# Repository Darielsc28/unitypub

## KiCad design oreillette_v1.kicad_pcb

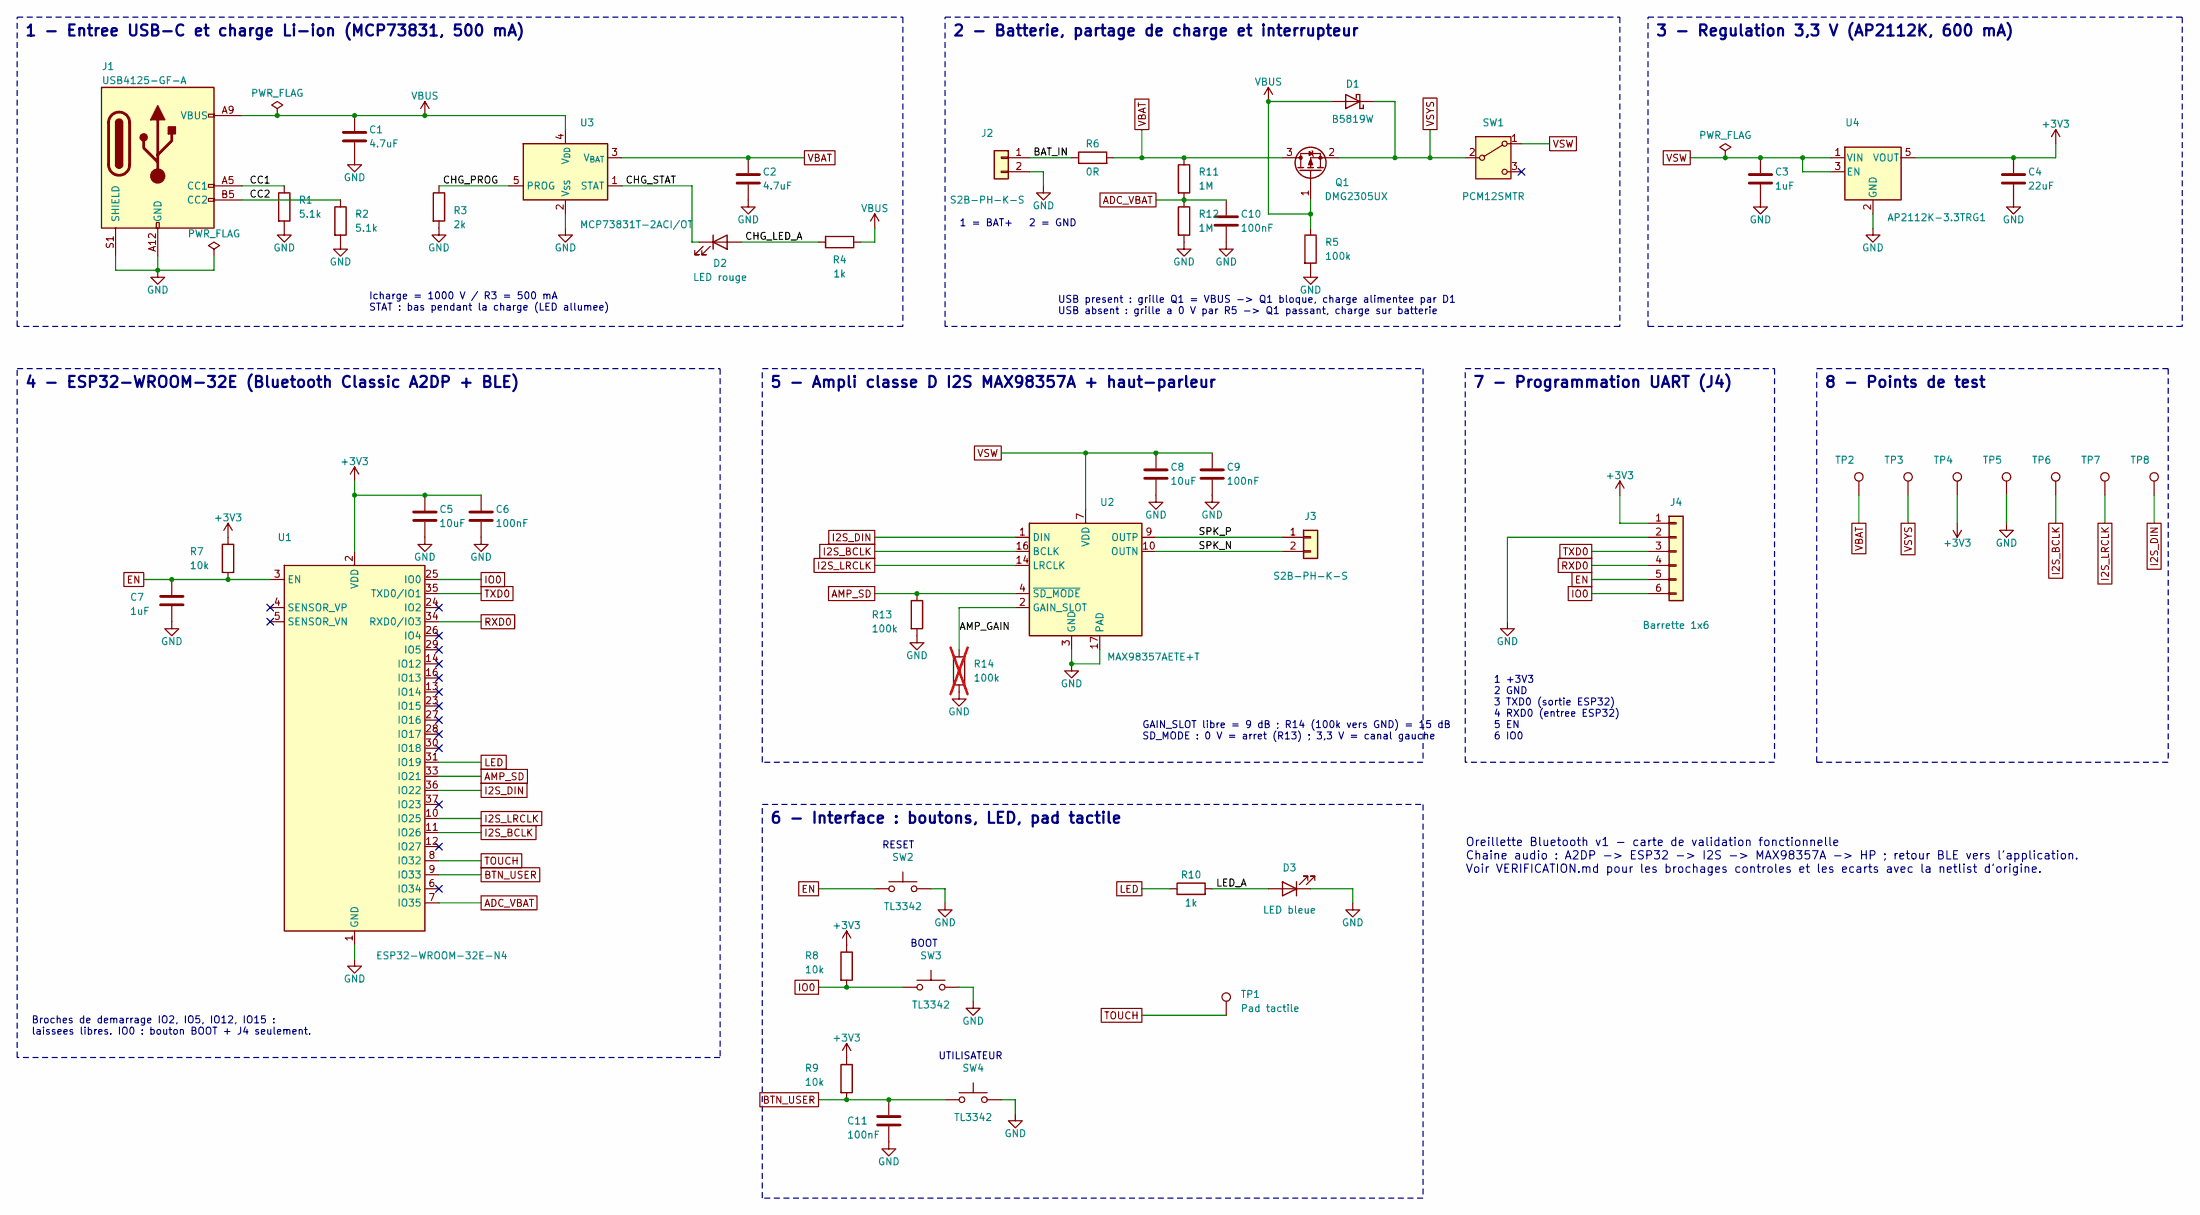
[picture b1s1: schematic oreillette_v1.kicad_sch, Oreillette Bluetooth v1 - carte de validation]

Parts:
C1, C2: 4.7uF; C_0603_1608Metric
C3, C7: 1uF; C_0603_1608Metric
C4: 22uF; C_0805_2012Metric
C5, C8: 10uF; C_0805_2012Metric
C6, C9, C10, C11: 100nF; C_0603_1608Metric
D1: B5819W; D_SOD-123
D2: LED rouge; LED_0603_1608Metric
D3: LED bleue; LED_0603_1608Metric
J1: USB4125-GF-A; USB_C_Receptacle_GCT_USB4125-xx-x_6P_TopMnt_Horizontal
J2, J3: S2B-PH-K-S; JST_PH_S2B-PH-K_1x02_P2.00mm_Horizontal
J4: Barrette 1x6; PinHeader_1x06_P2.54mm_Vertical
Q1: DMG2305UX; SOT-23
R1, R2: 5.1k; R_0603_1608Metric
R3: 2k; R_0603_1608Metric
R4, R10: 1k; R_0603_1608Metric
R5, R13: 100k; R_0603_1608Metric
R6: 0R; R_0603_1608Metric
R7, R8, R9: 10k; R_0603_1608Metric
R11, R12: 1M; R_0603_1608Metric
R14: 100k; R_0603_1608Metric; not fitted
SW1: PCM12SMTR; SW_SPDT_PCM12
SW2, SW3, SW4: TL3342; SW_SPST_TL3342
TP1: Pad tactile; TestPoint_Pad_D4.0mm
TP2: TP VBAT; TestPoint_Pad_D1.5mm
TP3: TP VSYS; TestPoint_Pad_D1.5mm
TP4: TP +3V3; TestPoint_Pad_D1.5mm
TP5: TP GND; TestPoint_Pad_D1.5mm
TP6: TP I2S_BCLK; TestPoint_Pad_D1.5mm
TP7: TP I2S_LRCLK; TestPoint_Pad_D1.5mm
TP8: TP I2S_DIN; TestPoint_Pad_D1.5mm
U1: ESP32-WROOM-32E-N4; ESP32-WROOM-32E
U2: MAX98357AETE+T; TQFN-16-1EP_3x3mm_P0.5mm_EP1.23x1.23mm
U3: MCP73831T-2ACI/OT; SOT-23-5
U4: AP2112K-3.3TRG1; SOT-23-5

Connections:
+3V3: C4.1, C5.1, C6.1, J4.1, R7.1, R8.1, R9.1, TP4.1, U1.2 (VDD), U4.5 (VOUT)
/AMP_GAIN: R14.1, U2.2 (GAIN_SLOT)
/BAT_IN: J2.1, R6.1
/CC1: J1.A5 (CC1), R1.1
/CC2: J1.B5 (CC2), R2.1
/CHG_LED_A: D2.2 (A), R4.2
/CHG_PROG: R3.1, U3.5 (PROG)
/CHG_STAT: D2.1 (K), U3.1 (STAT)
/LED_A: D3.2 (A), R10.2
/SPK_N: J3.2, U2.10 (OUTN)
/SPK_P: J3.1, U2.9 (OUTP)
ADC_VBAT: C10.1, R11.2, R12.1, U1.7 (IO35)
AMP_SD: R13.1, U1.33 (IO21), U2.4 (~SD_MODE)
BTN_USER: C11.1, R9.2, SW4.1, U1.9 (IO33)
EN: C7.1, J4.5, R7.2, SW2.1, U1.3 (EN)
GND: C1.2, C2.2, C3.2, C4.2, C5.2, C6.2, C7.2, C8.2, C9.2, C10.2, C11.2, D3.1 (K), J1.A12 (GND), J1.B12 (GND), J1.S1 (SHIELD), J2.2, J4.2, R1.2, R2.2, R3.2, R5.2, R12.2, R13.2, R14.2, SW2.2, SW3.2, SW4.2, TP5.1, U1.1 (GND), U1.15 (GND), U1.38 (GND), U1.39 (GND), U2.3 (GND), U2.11 (GND), U2.15 (GND), U2.17 (PAD), U3.2 (V_{SS}), U4.2 (GND)
I2S_BCLK: TP6.1, U1.11 (IO26), U2.16 (BCLK)
I2S_DIN: TP8.1, U1.36 (IO22), U2.1 (DIN)
I2S_LRCLK: TP7.1, U1.10 (IO25), U2.14 (LRCLK)
IO0: J4.6, R8.2, SW3.1, U1.25 (IO0)
LED: R10.1, U1.31 (IO19)
RXD0: J4.4, U1.34 (RXD0/IO3)
TOUCH: TP1.1, U1.8 (IO32)
TXD0: J4.3, U1.35 (TXD0/IO1)
VBAT: C2.1, Q1.3 (D), R6.2, R11.1, TP2.1, U3.3 (V_{BAT})
VBUS: C1.1, D1.2 (A), J1.A9 (VBUS), J1.B9 (VBUS), Q1.1 (G), R4.1, R5.1, U3.4 (V_{DD})
VSW: C3.1, C8.1, C9.1, SW1.1 (A), U2.7 (VDD), U2.8 (VDD), U4.1 (VIN), U4.3 (EN)
VSYS: D1.1 (K), Q1.2 (S), SW1.2 (B), TP3.1

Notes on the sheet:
1 - Entree USB-C et charge Li-ion (MCP73831, 500 mA)
Icharge = 1000 V / R3 = 500 mA STAT : bas pendant la charge (LED allumee)
2 - Batterie, partage de charge et interrupteur
1 = BAT+ 2 = GND
USB present : grille Q1 = VBUS -> Q1 bloque, charge alimentee par D1 USB absent : grille a 0 V par R5 -> Q1 passant, charge sur batterie
3 - Regulation 3,3 V (AP2112K, 600 mA)
4 - ESP32-WROOM-32E (Bluetooth Classic A2DP + BLE)
Broches de demarrage IO2, IO5, IO12, IO15 : laissees libres. IO0 : bouton BOOT + J4 seulement.
5 - Ampli classe D I2S MAX98357A + haut-parleur
GAIN_SLOT libre = 9 dB ; R14 (100k vers GND) = 15 dB SD_MODE : 0 V = arret (R13) ; 3,3 V = canal gauche
6 - Interface : boutons, LED, pad tactile
RESET
BOOT
UTILISATEUR
7 - Programmation UART (J4)
1 +3V3 2 GND 3 TXD0 (sortie ESP32) 4 RXD0 (entree ESP32) 5 EN 6 IO0
8 - Points de test
Oreillette Bluetooth v1 - carte de validation fonctionnelle Chaine audio : A2DP -> ESP32 -> I2S -> MAX98357A -> HP ; retour BLE vers l'application. Voir VERIFICATION.md pour les brochages controles et les ecarts avec la netlist d'origine.

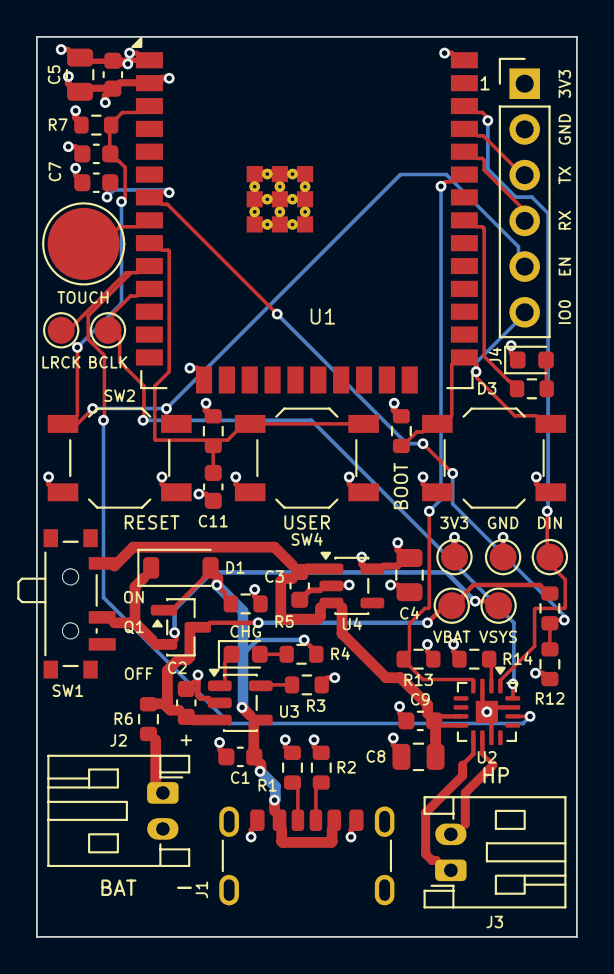
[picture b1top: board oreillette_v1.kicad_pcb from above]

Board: 4 copper layers, 30.0 x 50.0 mm, 49 parts (0 on the bottom side), 28 nets.

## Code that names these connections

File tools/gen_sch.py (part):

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wire(u3['2'], (90, 58))
gnd((90, 58))
wire(u3['5'], (72, 52))
label('CHG_PROG', (72.5, 52))
R('R3', 72, 55, '2k', 'Courant de charge 500 mA', refpos=(74, 55.5), valpos=(74, 57.5))
gnd((72, 58))
wire(u3['1'], (108, 52), (108, 60), (109, 60))
label('CHG_STAT', (98.5, 52))
place('D2', 'Device:LED', 112, 60, 0, 'LED rouge', FP['LED'], 'LED charge', refpos=(112, 63), valpos=(112, 65), just=None)
wire((115, 60), (126, 60))
label('CHG_LED_A', (115.5, 60))
R('R4', 129, 60, '1k', 'LED charge', rot=270, refpos=(129, 62.5), valpos=(129, 64.5))
wire((132, 60), (134, 60), (134, 58))
power('VBUS', (134, 58))
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wire(j2['2'], (144, 50), (144, 52))
gnd((144, 52))
wire(j2['1'], (148, 48))
label('BAT_IN', (142.5, 48))
R('R6', 151, 48, '0R', 'Shunt mesure courant batterie', rot=90, refpos=(151, 46), valpos=(151, 50))
text('1 = BAT+   2 = GND', (132, 58))
q1 = place('Q1', 'Transistor_FET:DMG2301L', 182, 50, 90, 'DMG2305UX', 'Package_TO_SOT_SMD:SOT-23',
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wire((160, 54), (170, 54))
C('C10', 170, 57, '100nF', 'Filtre mesure VBAT')
gnd((170, 60))
glabel('ADC_VBAT', (160, 54), 'L')
wire(q1['2'], (204, 48))
power('VBUS', (176, 40))
wire((176, 40), (185, 40))
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R('R5', 182, 61, '100k', 'Rappel grille Q1')
gnd((182, 64))
wire((199, 48), (199, 44))
glabel('VSYS', (199, 44), 'U')
sw1 = place('SW1', 'Switch:SW_SPDT', 208, 48, 0, 'PCM12SMTR', 'Button_Switch_SMD:SW_SPDT_PCM12',
            'Interrupteur marche/arret', refpos=(208, 43), valpos=(208, 53.5), just=None)
nc(sw1['3'])
wire(sw1['1'], (216, 46))
glabel('VSW', (216, 46), 'R')
text('USB present : grille Q1 = VBUS -> Q1 bloque, charge alimentee par D1\n'
     'USB absent : grille a 0 V par R5 -> Q1 passant, charge sur batterie', (146, 70.5))

# ===================================================== bloc 3 : regulation 3V3
OX[0] = 12
block('3 - Regulation 3,3 V (AP2112K, 600 mA)', 232, 28, 308, 72)
glabel('VSW', (238, 48), 'L')
u4 = place('U4', 'Regulator_Linear:AP2112K-3.3', 264, 50, 0, 'AP2112K-3.3TRG1', 'Package_TO_SOT_SMD:SOT-23-5',
           'LDO 3,3 V 600 mA', refpos=(260, 43), valpos=(266, 56.5),
           ds='https://www.diodes.com/assets/Datasheets/AP2112.pdf')
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gnd((140, sd[1] + 6))
ga = u2['2']
wire(ga, (146, ga[1]), (146, ga[1] + 6))
label('AMP_GAIN', (146, ga[1] + 3.5), 'R')
R('R14', 146, ga[1] + 9, '100k', 'Option gain 15 dB (non monte)', dnp=True, refpos=(148, ga[1] + 8), valpos=(148, ga[1] + 10))
gnd((146, ga[1] + 12))
vd = u2['7']
wire(vd, (164, 90))
wire((152, 90), (182, 90))
glabel('VSW', (152, 90), 'L')
C('C8', 174, 93, '10uF', 'Decouplage ampli', fp='C0805')
gnd((174, 96))
C('C9', 182, 93, '100nF', 'Decouplage ampli')
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           refpos=(196, u2['9'][1] - 3), valpos=(196, u2['9'][1] + 5.5), just=None)
wire(u2['9'], j3['1'])
wire(u2['10'], j3['2'])
label('SPK_P', (180, u2['9'][1]))
label('SPK_N', (180, u2['10'][1]))
text('GAIN_SLOT libre = 9 dB ; R14 (100k vers GND) = 15 dB\n'
     'SD_MODE : 0 V = arret (R13) ; 3,3 V = canal gauche', (172, 131))

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R('R8', 130, 163, '10k', 'Pull-up IO0', refpos=(124, 161.5), valpos=(124, 163.5))
power('+3V3', (130, 160))
text('BOOT', (139, 160.5))
glabel('BTN_USER', (126, 182), 'L')
s = button('SW4', 148, 182, 'Bouton utilisateur')
wire((126, 182), s['1'])
R('R9', 130, 179, '10k', 'Pull-up bouton', refpos=(124, 177.5), valpos=(124, 179.5))
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R('R10', 179, 152, '1k', 'LED etat', rot=90, refpos=(179, 150), valpos=(179, 154))
place('D3', 'Device:LED', 193, 152, 180, 'LED bleue', FP['LED'], 'LED etat', refpos=(193, 149), valpos=(193, 155), just=None)
wire((182, 152), (190, 152))
label('LED_A', (182.5, 152))
wire((196, 152), (202, 152), (202, 154))
gnd((202, 154))
glabel('TOUCH', (172, 170), 'L')
wire((172, 170), (184, 170))
place('TP1', 'Connector:TestPoint', 184, 170, 0, 'Pad tactile', 'TestPoint:TestPoint_Pad_D4.0mm', 'Electrode tactile',
      refpos=(186, 167), valpos=(186, 169))
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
